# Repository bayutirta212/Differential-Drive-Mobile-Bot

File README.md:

# Differential Drive Bot PCB

Custom PCB design for a compact Differential Drive Robot using ESP32 DevKit V1 (30 Pin).

## Features

- Dual motor differential drive system
- Encoder feedback support
- OLED display integration
- Ultrasonic obstacle detection
- GPIO expansion using multiplexer
- Line tracking sensor support
- Compact PCB layout
- ESP32-based control system

---

# Hardware Components

- ESP32 DevKit V1 (30 Pin)
- JGA12 N20 Motor Encoder
- DRV8833 Dual Motor Driver
- HC-SR04 Ultrasonic Sensor
- SSD1306 OLED Display
- CD74HC4067 16-Channel Multiplexer
- TCRT5000 IR Reflective Sensor

---

# System Overview

This robot uses a differential drive mechanism where each wheel is independently controlled using the DRV8833 motor driver.

The ESP32 handles:
- Motor control
- Encoder reading
- OLED communication
- Ultrasonic sensing
- Multiplexer control
- Sensor data processing

The CD74HC4067 multiplexer is used to expand input capability while minimizing GPIO usage.

---

# Pin Configuration

## DRV8833 Motor Driver

| ESP32 Pin | Function |
|---|---|
| GPIO16 | Motor A IN1 |
| GPIO17 | Motor A IN2 |
| GPIO05 | Motor B IN1 |
| GPIO23 | Motor B IN2 |

---

## Motor Encoder

| ESP32 Pin | Function |
|---|---|
| GPIO39 | Left Encoder A |
| GPIO36 | Left Encoder B |
| GPIO35 | Right Encoder A |
| GPIO34 | Right Encoder B |

---

## HC-SR04

| ESP32 Pin | Function |
|---|---|
| GPIO19 | Trigger |
| GPIO18 | Echo |

---

## SSD1306 OLED (I2C)

| ESP32 Pin | Function |
|---|---|
| GPIO21 | SDA |
| GPIO22 | SCL |

---

## CD74HC4067 Multiplexer

| ESP32 Pin | Function |
|---|---|
| GPIO27 | S0 |
| GPIO26 | S1 |
| GPIO25 | S2 |
| GPIO33 | S3 |
| GPIO32 | SIG |
| GIPO13 | EN |

---

# Repository Contents

- Schematic files
- PCB layout files
- Gerber files
- 3D PCB preview
- Wiring references

---

# Software Compatibility

This project can be programmed using:
- Arduino IDE
- PlatformIO

Recommended Libraries:
- Adafruit SSD1306
- Adafruit GFX
- ESP32Encoder
- NewPing

---

# Applications

- Line follower robot
- Obstacle avoidance robot
- Autonomous mobile robot
- Educational robotics platform

---

# Future Improvements

- IMU integration
- Battery monitoring
- PID motor control
- WiFi telemetry
- ROS compatibility

---

# License

This project is open-source under the MIT License.

---

# Author

Rafael Subally  
Student at Mechatronics Engineering Education  
Universitas Negeri Yogyakarta

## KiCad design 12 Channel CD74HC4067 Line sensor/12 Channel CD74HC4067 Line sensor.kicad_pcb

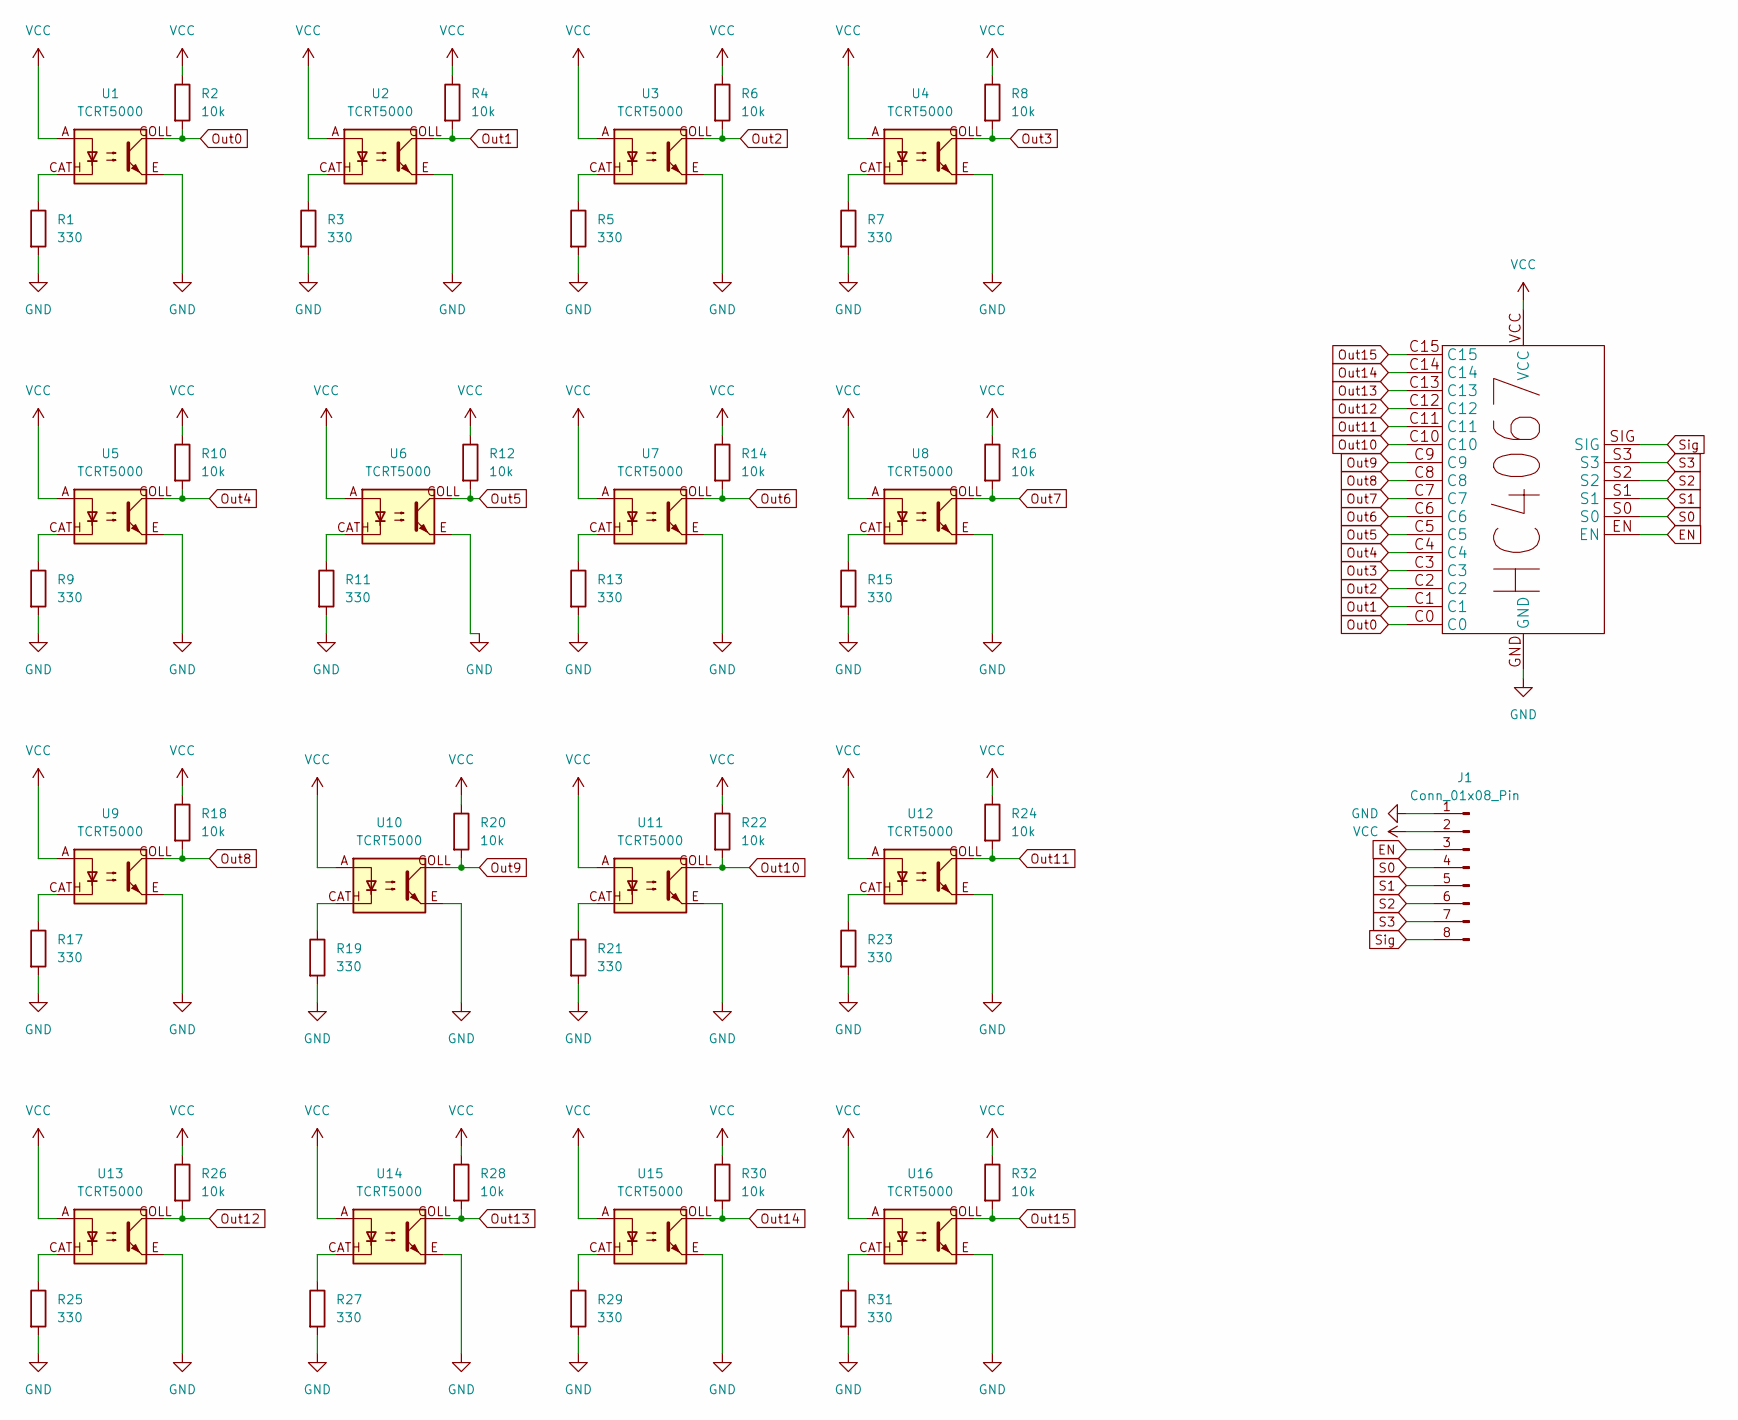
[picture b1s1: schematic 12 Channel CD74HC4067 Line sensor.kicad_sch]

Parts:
1: ANALOG_MUX_BREAKOUT_HC4067
J1: Conn_01x08_Pin; PinHeader_1x08_P2.54mm_Vertical
R1, R3, R5, R7, R9, R11, R13, R15, R17, R19, R21, R23, R25, R27, R29, R31: 330; R_1206_3216Metric_Pad1.30x1.75mm_HandSolder
R2, R4, R6, R8, R10, R12, R14, R16, R18, R20, R22, R24, R26, R28, R30, R32: 10k; R_1206_3216Metric_Pad1.30x1.75mm_HandSolder
U1, U2, U3, U4, U5, U6, U7, U8, U9, U10, U11, U12, U13, U14, U15, U16: TCRT5000; tcrt5000

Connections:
EN: 1.EN, J1.3
GND: 1.GND, J1.1, R1.2, R3.2, R5.2, R7.2, R9.2, R11.2, R13.2, R15.2, R17.2, R19.2, R21.2, R23.2, R25.2, R27.2, R29.2, R31.2, U1.E, U2.E, U3.E, U4.E, U5.E, U6.E, U7.E, U8.E, U9.E, U10.E, U11.E, U12.E, U13.E, U14.E, U15.E, U16.E
unnamed: R1.1, U1.CATH
unnamed: R3.1, U2.CATH
unnamed: R5.1, U3.CATH
unnamed: R7.1, U4.CATH
unnamed: R9.1, U5.CATH
unnamed: R11.1, U6.CATH
unnamed: R13.1, U7.CATH
unnamed: R15.1, U8.CATH
unnamed: R17.1, U9.CATH
unnamed: R19.1, U10.CATH
unnamed: R21.1, U11.CATH
unnamed: R23.1, U12.CATH
unnamed: R25.1, U13.CATH
unnamed: R27.1, U14.CATH
unnamed: R29.1, U15.CATH
unnamed: R31.1, U16.CATH
Out0: 1.C0, R2.2, U1.COLL
Out1: 1.C1, R4.2, U2.COLL
Out2: 1.C2, R6.2, U3.COLL
Out3: 1.C3, R8.2, U4.COLL
Out4: 1.C4, R10.2, U5.COLL
Out5: 1.C5, R12.2, U6.COLL
Out6: 1.C6, R14.2, U7.COLL
Out7: 1.C7, R16.2, U8.COLL
Out8: 1.C8, R18.2, U9.COLL
Out9: 1.C9, R20.2, U10.COLL
Out10: 1.C10, R22.2, U11.COLL
Out11: 1.C11, R24.2, U12.COLL
Out12: 1.C12, R26.2, U13.COLL
Out13: 1.C13, R28.2, U14.COLL
Out14: 1.C14, R30.2, U15.COLL
Out15: 1.C15, R32.2, U16.COLL
S0: 1.S0, J1.4
S1: 1.S1, J1.5
S2: 1.S2, J1.6
S3: 1.S3, J1.7
Sig: 1.SIG, J1.8
VCC: 1.VCC, J1.2, R2.1, R4.1, R6.1, R8.1, R10.1, R12.1, R14.1, R16.1, R18.1, R20.1, R22.1, R24.1, R26.1, R28.1, R30.1, R32.1, U1.A, U2.A, U3.A, U4.A, U5.A, U6.A, U7.A, U8.A, U9.A, U10.A, U11.A, U12.A, U13.A, U14.A, U15.A, U16.A

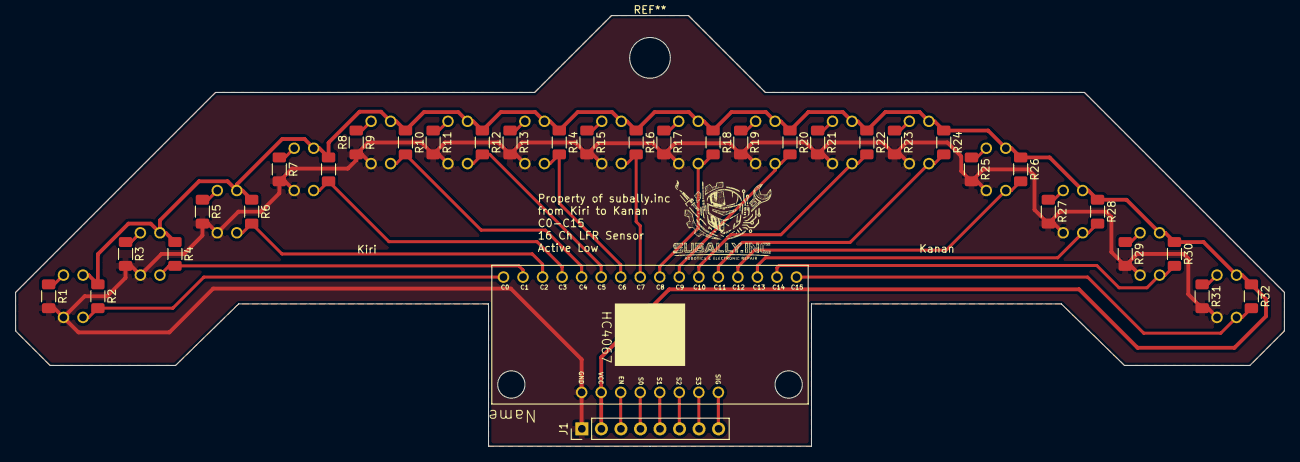
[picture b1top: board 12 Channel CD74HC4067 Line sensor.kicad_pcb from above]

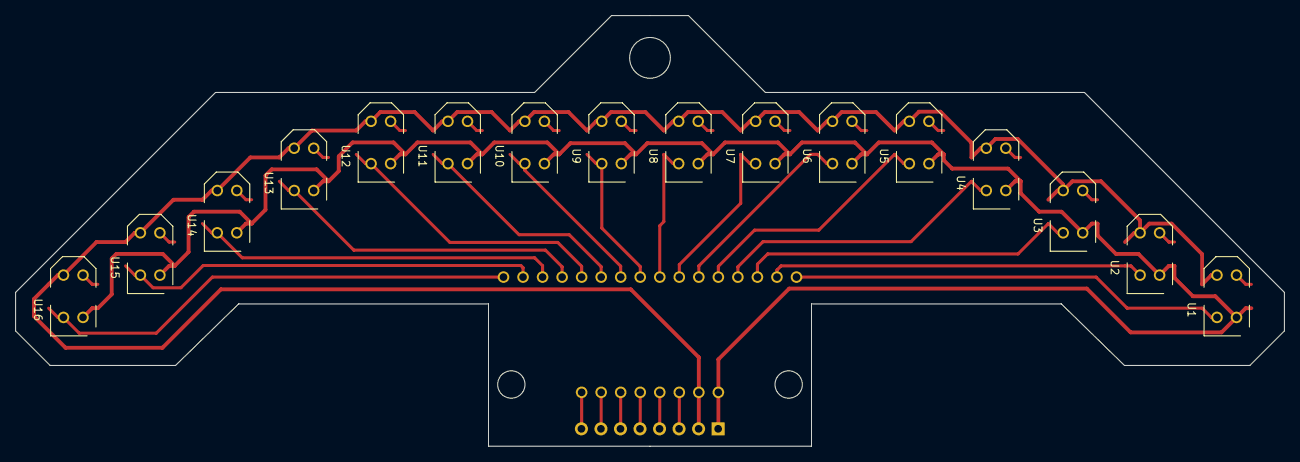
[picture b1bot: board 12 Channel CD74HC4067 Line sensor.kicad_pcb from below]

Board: 2 copper layers, 165.0 x 56.0 mm, 50 parts (16 on the bottom side), 40 nets.

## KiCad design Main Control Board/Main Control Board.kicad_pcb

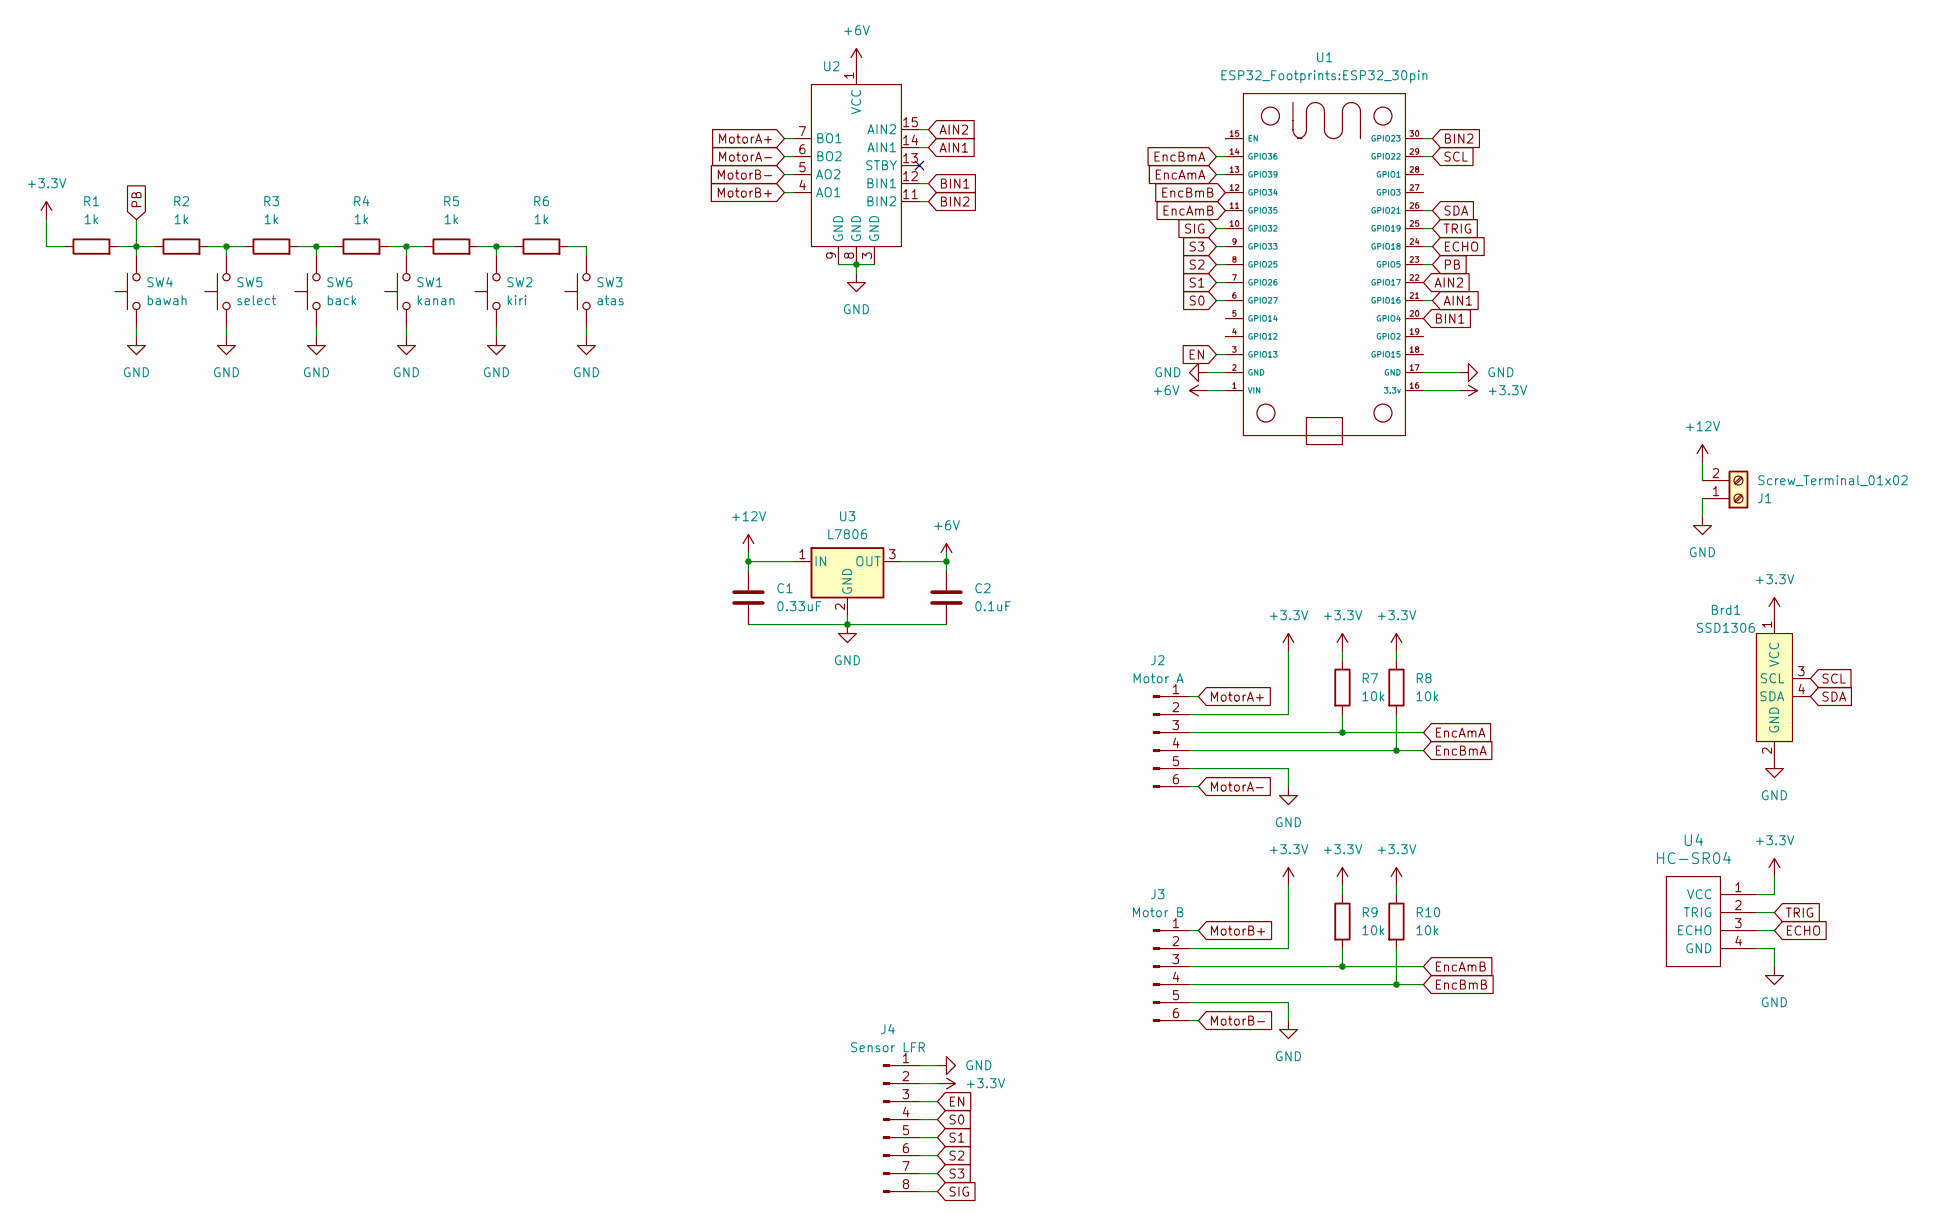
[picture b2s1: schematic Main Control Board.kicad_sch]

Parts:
Brd1: SSD1306; 128x64OLED
C1: 0.33uF; C_0805_2012Metric_Pad1.18x1.45mm_HandSolder
C2: 0.1uF; C_0805_2012Metric_Pad1.18x1.45mm_HandSolder
J1: Screw_Terminal_01x02; TerminalBlock_MaiXu_MX126-5.0-02P_1x02_P5.00mm
J2: Motor A; JST_XH_B6B-XH-A_1x06_P2.50mm_Vertical
J3: Motor B; JST_XH_B6B-XH-A_1x06_P2.50mm_Vertical
J4: Sensor LFR; PinHeader_1x08_P2.54mm_Vertical
R1, R2, R3, R4, R5, R6: 1k; R_1206_3216Metric_Pad1.30x1.75mm_HandSolder
R7, R8, R9, R10: 10k; R_1206_3216Metric_Pad1.30x1.75mm_HandSolder
SW1: kanan; SW_PUSH_6mm
SW2: kiri; SW_PUSH_6mm
SW3: atas; SW_PUSH_6mm
SW4: bawah; SW_PUSH_6mm
SW5: select; SW_PUSH_6mm
SW6: back; SW_PUSH_6mm
U1: ESP32_30pin
U2: DRV8833 Module
U3: L7806; TO-220-3_Horizontal_TabUp
U4: HC-SR04; PinHeader_1x04_P2.54mm_Vertical

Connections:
+3.3V: Brd1.1 (VCC), J2.2, J3.2, J4.2, R1.1, R7.1, R8.1, R9.1, R10.1, U1.16 (3.3v), U4.1 (VCC)
+6V: C2.1, U1.1 (VIN), U2.1 (VCC), U3.3 (OUT)
+12V: C1.1, J1.2, U3.1 (IN)
AIN1: U1.21 (GPIO16), U2.14 (AIN1)
AIN2: U1.22 (GPIO17), U2.15 (AIN2)
BIN1: U1.20 (GPIO4), U2.12 (BIN1)
BIN2: U1.30 (GPIO23), U2.11 (BIN2)
ECHO: U1.24 (GPIO18), U4.3 (ECHO)
EN: J4.3, U1.3 (GPIO13)
EncAmA: J2.3, R7.2, U1.13 (GPIO39)
EncAmB: J3.3, R9.2, U1.11 (GPIO35)
EncBmA: J2.4, R8.2, U1.14 (GPIO36)
EncBmB: J3.4, R10.2, U1.12 (GPIO34)
GND: Brd1.2 (GND), C1.2, C2.2, J1.1, J2.5, J3.5, J4.1, SW1.1, SW2.1, SW3.1, SW4.1, SW5.1, SW6.1, U1.2 (GND), U1.17 (GND), U2.3 (GND), U2.8 (GND), U2.9 (GND), U3.2 (GND), U4.4 (GND)
MotorA+: J2.1, U2.7 (BO1)
MotorA-: J2.6, U2.6 (BO2)
MotorB+: J3.1, U2.4 (AO1)
MotorB-: J3.6, U2.5 (AO2)
unnamed: R2.2, R3.1, SW5.2
unnamed: R3.2, R4.1, SW6.2
unnamed: R4.2, R5.1, SW1.2
unnamed: R5.2, R6.1, SW2.2
unnamed: R6.2, SW3.2
PB: R1.2, R2.1, SW4.2, U1.23 (GPIO5)
S0: J4.4, U1.6 (GPIO27)
S1: J4.5, U1.7 (GPIO26)
S2: J4.6, U1.8 (GPIO25)
S3: J4.7, U1.9 (GPIO33)
SCL: Brd1.3 (SCL), U1.29 (GPIO22)
SDA: Brd1.4 (SDA), U1.26 (GPIO21)
SIG: J4.8, U1.10 (GPIO32)
TRIG: U1.25 (GPIO19), U4.2 (TRIG)

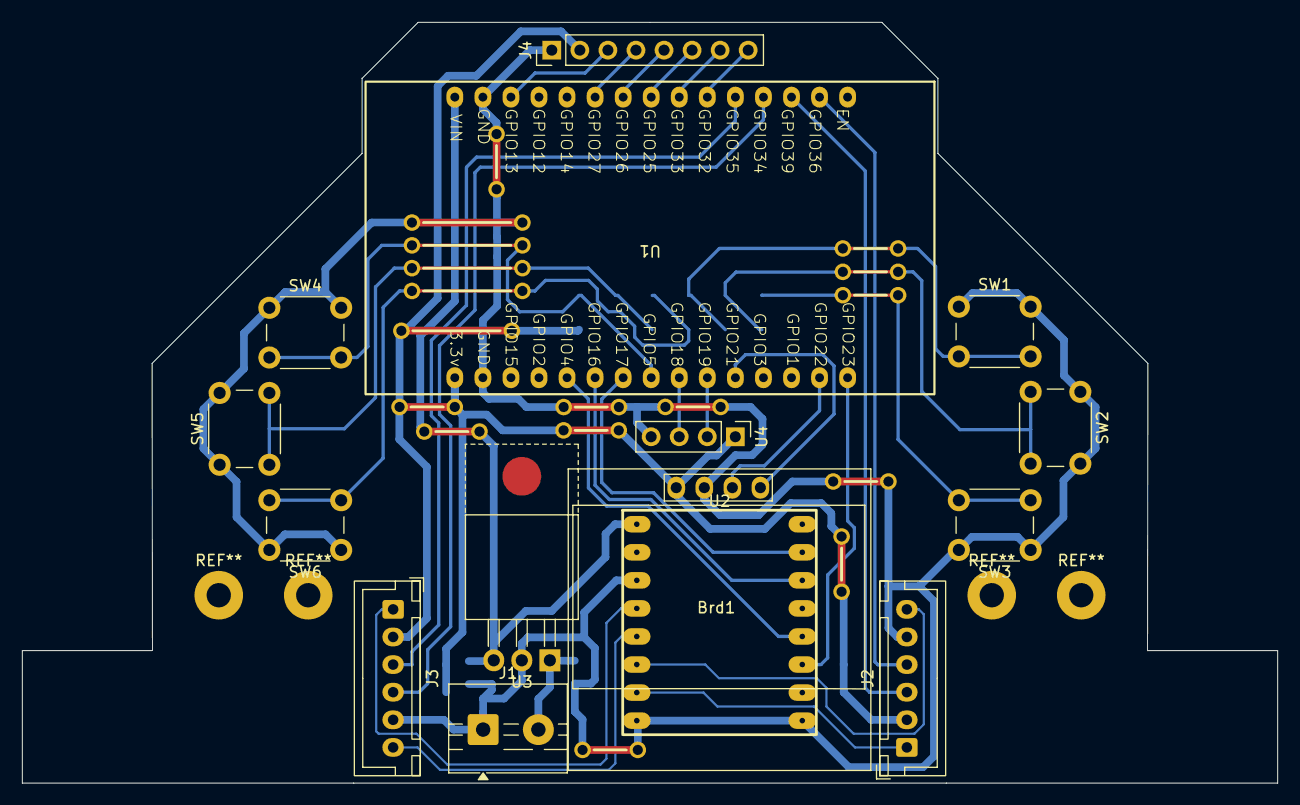
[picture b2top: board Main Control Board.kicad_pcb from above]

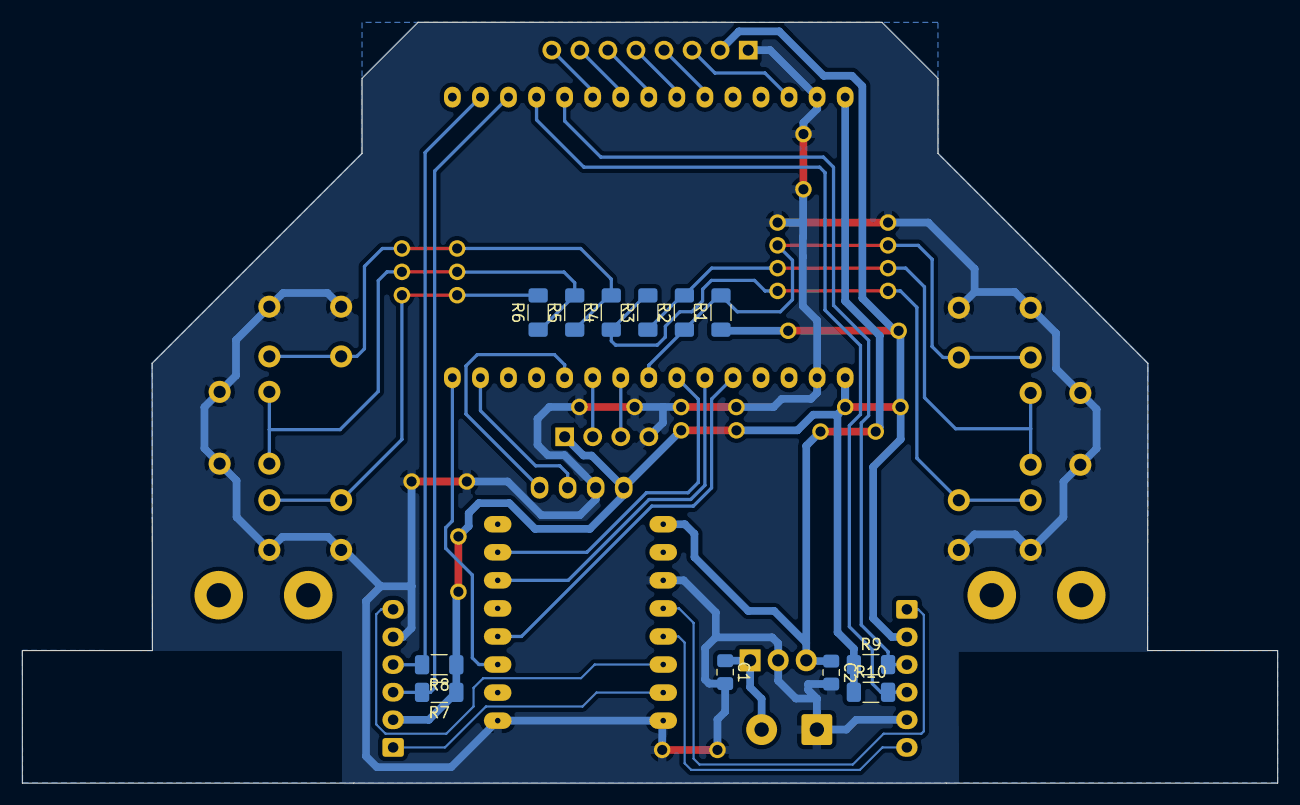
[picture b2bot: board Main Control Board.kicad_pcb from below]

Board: 4 copper layers, 113.6 x 68.9 mm, 27 parts (12 on the bottom side), 32 nets.

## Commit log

2026-05-11 Update README with project details and documentation
    Added detailed documentation for the Differential Drive Bot PCB, including features, hardware components, system overview, pin configuration, repository contents, software compatibility, applications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
2026-05-11 Revise ESP32 pin assignments in README
    Updated ESP32 pin assignments for various components and removed the TCRT5000 section.
